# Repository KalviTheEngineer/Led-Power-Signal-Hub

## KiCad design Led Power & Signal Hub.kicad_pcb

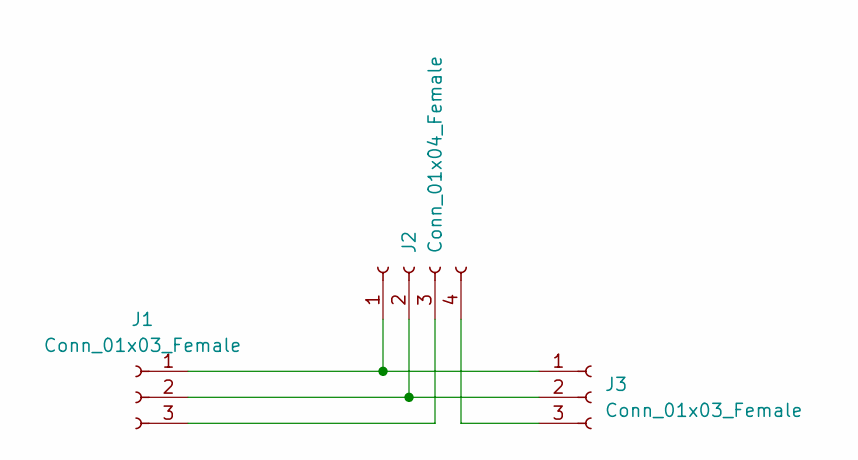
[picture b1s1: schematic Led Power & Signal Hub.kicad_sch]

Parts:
J1, J3: Conn_01x03_Female; Molex_Mini-Fit_Jr_5569-04A2_2x02_P4.20mm_Horizontal
J2: Conn_01x04_Female; Gniazdo WF kątowe

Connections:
unnamed: J1.1, J2.1, J3.1
unnamed: J1.2, J2.2, J3.2
unnamed: J1.3, J2.3
unnamed: J2.4, J3.3

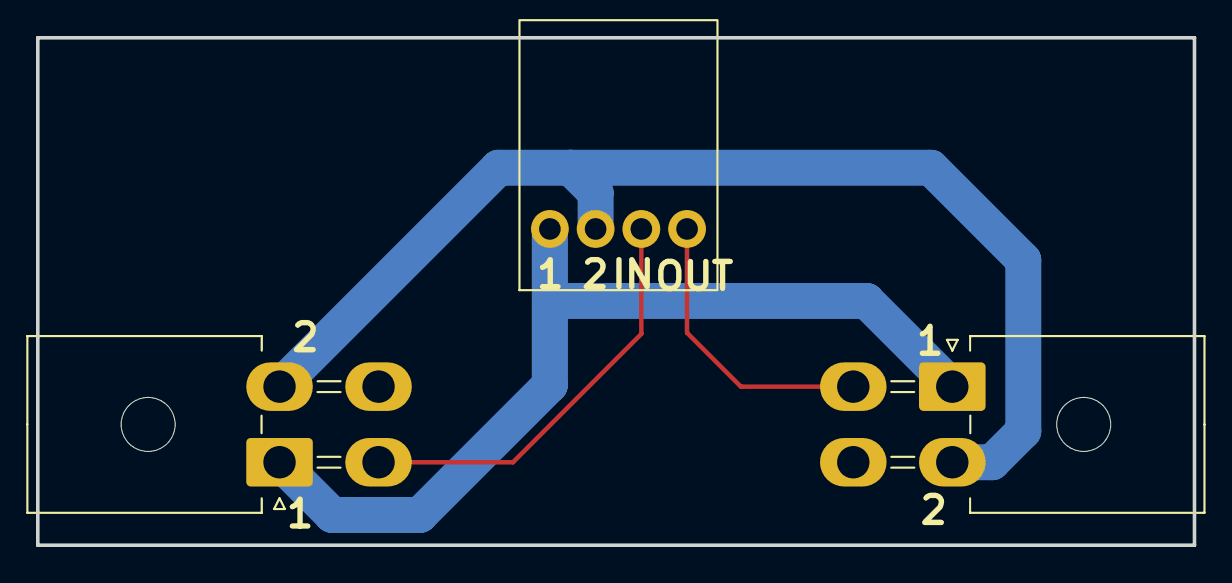
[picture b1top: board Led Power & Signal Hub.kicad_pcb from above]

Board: 2 copper layers, 64.3 x 28.2 mm, 3 parts (0 on the bottom side), 4 nets.

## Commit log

2023-06-29 Gotowe PCB
